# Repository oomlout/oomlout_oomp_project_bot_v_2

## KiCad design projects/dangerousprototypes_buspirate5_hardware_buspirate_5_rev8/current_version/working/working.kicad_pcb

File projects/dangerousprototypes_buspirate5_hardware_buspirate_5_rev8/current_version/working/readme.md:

# buspirate5_hardware
 
## summary 
* id: dangerousprototypes_buspirate5_hardware_buspirate_5_rev8
* user: dangerousprototypes
* name: buspirate5_hardware
* board: buspirate_5_rev8
* repo: https://github.com/DangerousPrototypes/BusPirate5-hardware
* src_file_repo_kicad_pcb: pcb/BusPirate-5-rev8.kicad_pcb
* src_file_repo_kicad_pcb_link: https://github.com/DangerousPrototypes/BusPirate5-hardware/tree/main/pcb/BusPirate-5-rev8.kicad_pcb

* src_file_repo_sch: debug-station/programming_pin_mount.v1.0.sch
* src_file_repo_sch_link: https://github.com/DangerousPrototypes/BusPirate5-hardware/tree/main/debug-station/programming_pin_mount.v1.0.sch
* full details link: https://github.com/oomlout/oomlout_oomp_project_bot_v_2/tree/main/projects/dangerousprototypes_buspirate5_hardware_buspirate_5_rev8/current_version/working  

## schematic  
  
[schematic (pdf)](working_schematic.pdf) 

[schematic 1 (pdf)](working_1_schematic.pdf) 

[schematic 2 (pdf)](working_2_schematic.pdf) 

[schematic 3 (pdf)](working_3_schematic.pdf) 

[schematic 4 (pdf)](working_4_schematic.pdf) 

[schematic 5 (pdf)](working_5_schematic.pdf) 

## pcb  

[board (pdf)](working.pdf)  

## working_bom
| Id | Designator | Footprint | Quantity | Designation | Supplier and ref |  | None | 
| --- | --- | --- | --- | --- | --- | --- | --- | 
| 1 | LED702,LED715,LED714,LED703,LED705,LED718,LED706,LED710,LED713 | SK6812-mini-e | 9 | SK6812-mini-e |  |  | [''] | 
| 2 | C402,C101,C202,C201,C401,C102,C404,C407 | C_0402_1005Metric | 8 | 4.7uF |  |  | [''] | 
| 3 | C313,C308,C315,C304,C403,C314,C309,C112,C114,C110,C111,C113,C103,C118,C705,C708,C704,C706,C710,C712,C703,C701,C117,C501,C116,C715,C714,C716,C717,C718,C318,C502,C713,C406,C115,C707,C602,C605,C702,C311,C312,C503,C306,C307,C301,C302,C305,C303,C316,C317,C310,C414,C415,C416 | C_0402_1005Metric | 54 | 0.1uF |  |  | [''] | 
| 4 | C107,C108,C109,C104,C405,C601,C413 | C_0402_1005Metric | 7 | 2.2uF |  |  | [''] | 
| 5 | C106,C105 | C_0402_1005Metric | 2 | 15pF |  |  | [''] | 
| 6 | U301,U304,U305,U307,U306,U303,U302,U308 | SOT-363_SC-70-6 | 8 | SN74LVC1T45DCK |  |  | [''] | 
| 7 | R203,R202 | R_0402_1005Metric | 2 | 22R |  |  | [''] | 
| 8 | R204,R201 | R_0402_1005Metric | 2 | 5.1K |  |  | [''] | 
| 9 | L201 | L_0805_2012Metric | 1 | 1.5A |  |  | [''] | 
| 10 | R407,R501,R402,R406,R104,R105,R410,R611,R609,R606,R610,R613,R106,R312,R414,R415 | R_0402_1005Metric | 16 | 10K |  |  | [''] | 
| 11 | R103,R608,R612,R208 | R_0402_1005Metric | 4 | 200R |  |  | [''] | 
| 12 | U103 | RP2040-QFN-56 | 1 | RP2040 |  |  | [''] | 
| 13 | U501,U502 | TSSOP-16_4.4x5mm_P0.65mm | 2 | 74HC595 |  |  | [''] | 
| 14 | RN302,RN307,RN304,RN310 | R_Array_Convex_4x0402 | 4 | 1M |  |  | [''] | 
| 15 | R209 | R_0805_2012Metric | 1 | 33R |  |  | [''] | 
| 16 | U102 | SOP-8_5.28x5.23mm_P1.27mm | 1 | W25Q128JVSIQ |  |  | [''] | 
| 17 | U310,U309 | TSSOP-14_4.4x5mm_P0.65mm | 2 | 74HC4066 |  |  | [''] | 
| 18 | R101,R602,R603,R502 | R_0402_1005Metric | 4 | 1K |  |  | [''] | 
| 19 | FID1,FID2,FID4,FID5,FID3 | Fiducial_1mm_Mask2mm | 5 | Fiducial |  |  | [''] | 
| 20 | J201 | PinSocket_1x03_P2.54mm_Vertical | 1 | Conn_01x03 |  |  | [''] | 
| 21 | R102 | R_0402_1005Metric | 1 | DNF |  |  | [''] | 
| 22 | J302 | JST_SH_SM09B-SRSS-TB_1x09-1MP_P1.00mm_Horizontal | 1 | Conn_01x09 |  |  | [''] | 
| 23 | U503 | TSSOP-20_4.4x6.5mm_P0.65mm | 1 | 74HCT245PW |  |  | [''] | 
| 24 | Y101 | Crystal_SMD_3225-4Pin_3.2x2.5mm | 1 | 12Mhz |  |  | [''] | 
| 25 | Q202 | SOT-23 | 1 | 2N7002 |  |  | [''] | 
| 26 | L100 | L_0603_1608Metric | 1 | 22uH |  |  | [''] | 
| 27 | J101 | TF-01A_C91145 | 1 | Micro_SD_Card_TF-01A_C91145 |  |  | [''] | 
| 28 | SW101 | SW_SPST_PTS810 | 1 | SW_SPST |  |  | [''] | 
| 29 | D601,D401,D603,D602 | D_SOD-323 | 4 | 1N4148WS |  |  | [''] | 
| 30 | R405,R409,R408,R605,R604 | R_0402_1005Metric | 5 | 33K |  |  | [''] | 
| 31 | R412,R401 | R_0402_1005Metric | 2 | 100K |  |  | [''] | 
| 32 | R403 | R_0402_1005Metric | 1 | 102K |  |  | [''] | 
| 33 | U601,U404,U603 | SOT-23-5 | 3 | GS6001 |  |  | [''] | 
| 34 | R601 | R_2512_6332Metric_Pad1.40x3.35mm_HandSolder | 1 | 0R2 |  |  | [''] | 
| 35 | C603 | C_0402_1005Metric | 1 | DNF |  |  | [''] | 
| 36 | U602 | SOT-23-5 | 1 | RS8901XF |  |  | [''] | 
| 37 | Q402,Q602 | SOT-23 | 2 | WST3423 |  |  | [''] | 
| 38 | U403 | SOT-23-5 | 1 | AP2127 |  |  | [''] | 
| 39 | Q601 | SOT-363_SC-70-6 | 1 | MMDT3906 |  |  | [''] | 
| 40 | Q401 | SOT-363_SC-70-6 | 1 | BCM857 |  |  | [''] | 
| 41 | RN309,RN301,RN306,RN315,RN318,RN317,RN305,RN400,RN401,RN402 | R_Array_Convex_4x0402 | 10 | 330R |  |  | [''] | 
| 42 | U402 | TSSOP-24_4.4x7.8mm_P0.65mm | 1 | 74HC4067 |  |  | [''] | 
| 43 | RN303,RN308 | R_Array_Convex_4x0402 | 2 | 100K |  |  | [''] | 
| 44 | J202 | HRO_TYPE-C-31-M-12 | 1 | TYPE-C-31-M-12 |  |  | [''] | 
| 45 | RN313,RN314,RN312,RN311 | R_Array_Convex_4x0402 | 4 | 10K |  |  | [''] | 
| 46 | LED707,LED716,LED717,LED712,LED708,LED701,LED704 | SK6812-side-a_b | 7 | SK6812-side-a_b |  |  | [''] | 
| 47 | R316,R416 | R_0402_1005Metric | 2 | 330R |  |  | [''] | 
| 48 | U401 | SOT-89-3 | 1 | ME6211A33PG-N |  |  | [''] | 
| 49 | C408 | C_0402_1005Metric | 1 | 120pF |  |  | [''] | 
| 50 | R404 | R_0402_1005Metric | 1 | 133K |  |  | [''] | 
| 51 | J301 | PinHeader_1x10_P2.54mm_Vertical | 1 | Conn_01x10 |  |  | [''] | 
| 52 | SW102 | GT-TC026X-HXXX-LX | 1 | 4P_button_sw |  |  | [''] | 
| 53 | LCD201 | TFT_20_QT200H1201 | 1 | TFT_20_QT200H1201 |  |  | [''] | 
| 54 | logo1 | logo_fcc | 1 | fcc_logo |  |  | [''] | 

## bom_schematic
| Ref | Qnty | Value | Cmp name | Footprint | Description | Vendor | DNP | 
| --- | --- | --- | --- | --- | --- | --- | --- | 
| C101, C102, C201, C202, C401, C402, C404, C407 | 8 | 4.7uF | C_Small | Capacitor_SMD:C_0402_1005Metric | Unpolarized capacitor, small symbol |  |  | 
| C103, C110, C111, C112, C113, C114, C115, C116, C117, C118, C301, C302, C303, C304, C305, C306, C307, C308, C309, C310, C311, C312, C313, C314, C315, C316, C317, C318, C403, C406, C414, C415, C416, C501, C502, C503, C602, C605, C701, C702, C703, C704, C705, C706, C707, C708, C710, C712, C713, C714, C715, C716, C717, C718 | 54 | 0.1uF | C_Small | Capacitor_SMD:C_0402_1005Metric | Unpolarized capacitor, small symbol |  |  | 
| C104, C107, C108, C109, C405, C413, C601 | 7 | 2.2uF | C_Small | Capacitor_SMD:C_0402_1005Metric | Unpolarized capacitor, small symbol |  |  | 
| C105, C106 | 2 | 15pF | C_Small | Capacitor_SMD:C_0402_1005Metric | Unpolarized capacitor, small symbol |  |  | 
| C408 | 1 | 120pF | C_Small | Capacitor_SMD:C_0402_1005Metric | Unpolarized capacitor, small symbol |  |  | 
| C603 | 1 | DNF | C_Small | Capacitor_SMD:C_0402_1005Metric | Unpolarized capacitor, small symbol |  |  | 
| D401, D601, D602, D603 | 4 | 1N4148WS | 1N4148WS | Diode_SMD:D_SOD-323 | 75V 0.15A Fast switching Diode, SOD-323 |  |  | 
| FID1, FID2, FID3, FID4, FID5 | 5 | Fiducial | Fiducial | Fiducial:Fiducial_1mm_Mask2mm | Fiducial Marker |  |  | 
| H1, H2, H3, H4 | 4 | MountingHole | MountingHole | MountingHole:MountingHole_3.2mm_M3 | Mounting Hole without connection |  |  | 
| J101 | 1 | Micro_SD_Card_TF-01A_C91145 | Micro_SD_Card_TF-01A_C91145-dp-microsd | dp-microsd:TF-01A_C91145 |  |  |  | 
| J201 | 1 | Conn_01x03 | Conn_01x03 | Connector_PinSocket_2.54mm:PinSocket_1x03_P2.54mm_Vertical | Generic connector, single row, 01x03, script generated (kicad-library-utils/schlib/autogen/connector/) |  |  | 
| J202 | 1 | TYPE-C-31-M-12 | TYPE-C-31-M-12-usb-c | HRO_TYPE-C-31-M-12 |  |  |  | 
| J301 | 1 | Conn_01x10 | Conn_01x10 | Connector_PinHeader_2.54mm:PinHeader_1x10_P2.54mm_Vertical | Generic connector, single row, 01x10, script generated (kicad-library-utils/schlib/autogen/connector/) |  |  | 
| J302 | 1 | Conn_01x09 | Conn_01x09 | Connector_JST:JST_SH_SM09B-SRSS-TB_1x09-1MP_P1.00mm_Horizontal | Generic connector, single row, 01x09, script generated (kicad-library-utils/schlib/autogen/connector/) |  |  | 
| L100 | 1 | 22uH | L_Small | Inductor_SMD:L_0603_1608Metric | Inductor, small symbol |  |  | 
| L201 | 1 | 1.5A | Ferrite_Bead_Small-kicad5-device | Inductor_SMD:L_0805_2012Metric |  |  |  | 
| LCD201 | 1 | TFT_20_QT200H1201 | TFT_20_QT200H1201-dp-lcd | dp-lcd:TFT_20_QT200H1201 |  |  |  | 
| LED1, LED2, LED3, LED4, LED5, LED6, LED7, LED8, LED9 | 9 | SK6812-mini-e | SK6812-mini-e-dp-LED | dp-LED:SK6812-mini-e |  |  |  | 
| LED701, LED704, LED707, LED708, LED712, LED716, LED717 | 7 | SK6812-side-a_b | SK6812-side-a_b-dp-LED | dp-LED:SK6812-side-a_b |  |  |  | 
| logo1 | 1 | fcc_logo | fcc_logo-DP_logo_kicad | dp-logo:logo_fcc |  |  |  | 
| Q1 | 1 | 2N7002 | BSS138 | Package_TO_SOT_SMD:SOT-23 | 50V Vds, 0.22A Id, N-Channel MOSFET, SOT-23 |  |  | 
| Q401 | 1 | BCM857 | Q_DUAL_PNP_PNP_E1B1C2E2B2C1-kicad5-device | Package_TO_SOT_SMD:SOT-363_SC-70-6 |  |  |  | 
| Q402, Q602 | 2 | WST3423 | AO3401A | Package_TO_SOT_SMD:SOT-23 | -4.0A Id, -30V Vds, P-Channel MOSFET, SOT-23 |  |  | 
| Q601 | 1 | MMDT3906 | Q_DUAL_PNP_PNP_E1B1C2E2B2C1-kicad5-device | Package_TO_SOT_SMD:SOT-363_SC-70-6 |  |  |  | 
| R1, R2, R4, R104, R105, R402, R406, R407, R410, R414, R415, R606, R609, R610, R611, R613 | 16 | 10K | R_Small | Resistor_SMD:R_0402_1005Metric | Resistor, small symbol |  |  | 
| R3, R416 | 2 | 330R | R_Small | Resistor_SMD:R_0402_1005Metric | Resistor, small symbol |  |  | 
| R5, R101, R602, R603 | 4 | 1K | R_Small | Resistor_SMD:R_0402_1005Metric | Resistor, small symbol |  |  | 
| R102 | 1 | DNF | R_Small | Resistor_SMD:R_0402_1005Metric | Resistor, small symbol |  |  | 
| R103, R208, R608, R612 | 4 | 200R | R_Small | Resistor_SMD:R_0402_1005Metric | Resistor, small symbol |  |  | 
| R201, R204 | 2 | 5.1K | R_Small | Resistor_SMD:R_0402_1005Metric | Resistor, small symbol |  |  | 
| R202, R203 | 2 | 22R | R_Small | Resistor_SMD:R_0402_1005Metric | Resistor, small symbol |  |  | 
| R209 | 1 | 33R | R_Small | Resistor_SMD:R_0805_2012Metric | Resistor, small symbol |  |  | 
| R401, R412 | 2 | 100K | R_Small | Resistor_SMD:R_0402_1005Metric | Resistor, small symbol |  |  | 
| R403 | 1 | 102K | R_Small | Resistor_SMD:R_0402_1005Metric | Resistor, small symbol |  |  | 
| R404 | 1 | 133K | R_Small | Resistor_SMD:R_0402_1005Metric | Resistor, small symbol |  |  | 
| R405, R408, R409, R604, R605 | 5 | 33K | R_Small | Resistor_SMD:R_0402_1005Metric | Resistor, small symbol |  |  | 
| R601 | 1 | 0R2 | R | Resistor_SMD:R_2512_6332Metric_Pad1.40x3.35mm_HandSolder | Resistor |  |  | 
| RN301, RN305, RN306, RN309, RN315, RN317, RN318, RN400, RN401, RN402 | 10 | 330R | R_Array-dp-rarray | Resistor_SMD:R_Array_Convex_4x0402 |  |  |  | 
| RN302, RN304, RN307, RN310 | 4 | 1M | R_Array-dp-rarray | Resistor_SMD:R_Array_Convex_4x0402 |  |  |  | 
| RN303, RN308 | 2 | 100K | R_Array-dp-rarray | Resistor_SMD:R_Array_Convex_4x0402 |  |  |  | 
| RN311, RN312, RN313, RN314 | 4 | 10K | R_Array-dp-rarray | Resistor_SMD:R_Array_Convex_4x0402 |  |  |  | 
| SW101 | 1 | SW_SPST | SW_SPST | Button_Switch_SMD:SW_SPST_PTS810 | Single Pole Single Throw (SPST) switch |  |  | 
| SW102 | 1 | 4P_button_sw | 4P_button_sw-dp-switch | dp-switch:GT-TC026X-HXXX-LX |  |  |  | 
| U102 | 1 | W25Q128JVSIQ | xm25qh128a-dp-memory | Package_SO:SOP-8_5.28x5.23mm_P1.27mm |  |  |  | 
| U103 | 1 | RP2040 | RP2040-RP_Silicon | RP_Silicon:RP2040-QFN-56 |  |  |  | 
| U301, U302, U303, U304, U305, U306, U307, U308 | 8 | SN74LVC1T45DCK | SN74LVC1T45DCK | Package_TO_SOT_SMD:SOT-363_SC-70-6 | Single-Bit Dual-Supply Bus Transceiver With Configurable Voltage Translation and 3-State Outputs, SOT-363 |  |  | 
| U309, U310 | 2 | 74HC4066 | 4066-4xxx_IEEE | Package_SO:TSSOP-14_4.4x5mm_P0.65mm |  |  |  | 
| U401 | 1 | ME6211A33PG-N | AP2204RA-3.3 | Package_TO_SOT_SMD:SOT-89-3 | 150mA low dropout linear regulator, wide input voltage range, 3.3V fixed positive output, SOT-89-3 package |  |  | 
| U402 | 1 | 74HC4067 | CD74HC4067M | Package_SO:TSSOP-24_4.4x7.8mm_P0.65mm | High-Speed CMOS Logic 16-Channel Analog Multiplexer/Demultiplexer, SOIC-24 |  |  | 
| U403 | 1 | AP2127 | MCP1824-dp-vreg | Package_TO_SOT_SMD:SOT-23-5 |  |  |  | 
| U404, U601, U603 | 3 | GS6001 | MCP6001-OT | Package_TO_SOT_SMD:SOT-23-5 | 1MHz, Low-Power Op Amp, SOT-23-5 |  |  | 
| U501, U502 | 2 | 74HC595 | 74AHCT595 | Package_SO:TSSOP-16_4.4x5mm_P0.65mm | 8-bit serial in/out Shift Register 3-State Outputs |  |  | 
| U503 | 1 | 74HCT245PW | 74HC245 | Package_SO:TSSOP-20_4.4x6.5mm_P0.65mm | Octal BUS Transceivers, 3-State outputs |  |  | 
| U602 | 1 | RS8901XF | MCP6001x-LT | Package_TO_SOT_SMD:SOT-23-5 | 1 MHz, Low-Power Op Amp, SC-70-5 |  |  | 
| Y101 | 1 | 12Mhz | Crystal_GND24_Small | Crystal:Crystal_SMD_3225-4Pin_3.2x2.5mm | Four pin crystal, GND on pins 2 and 4, small symbol |  |  |

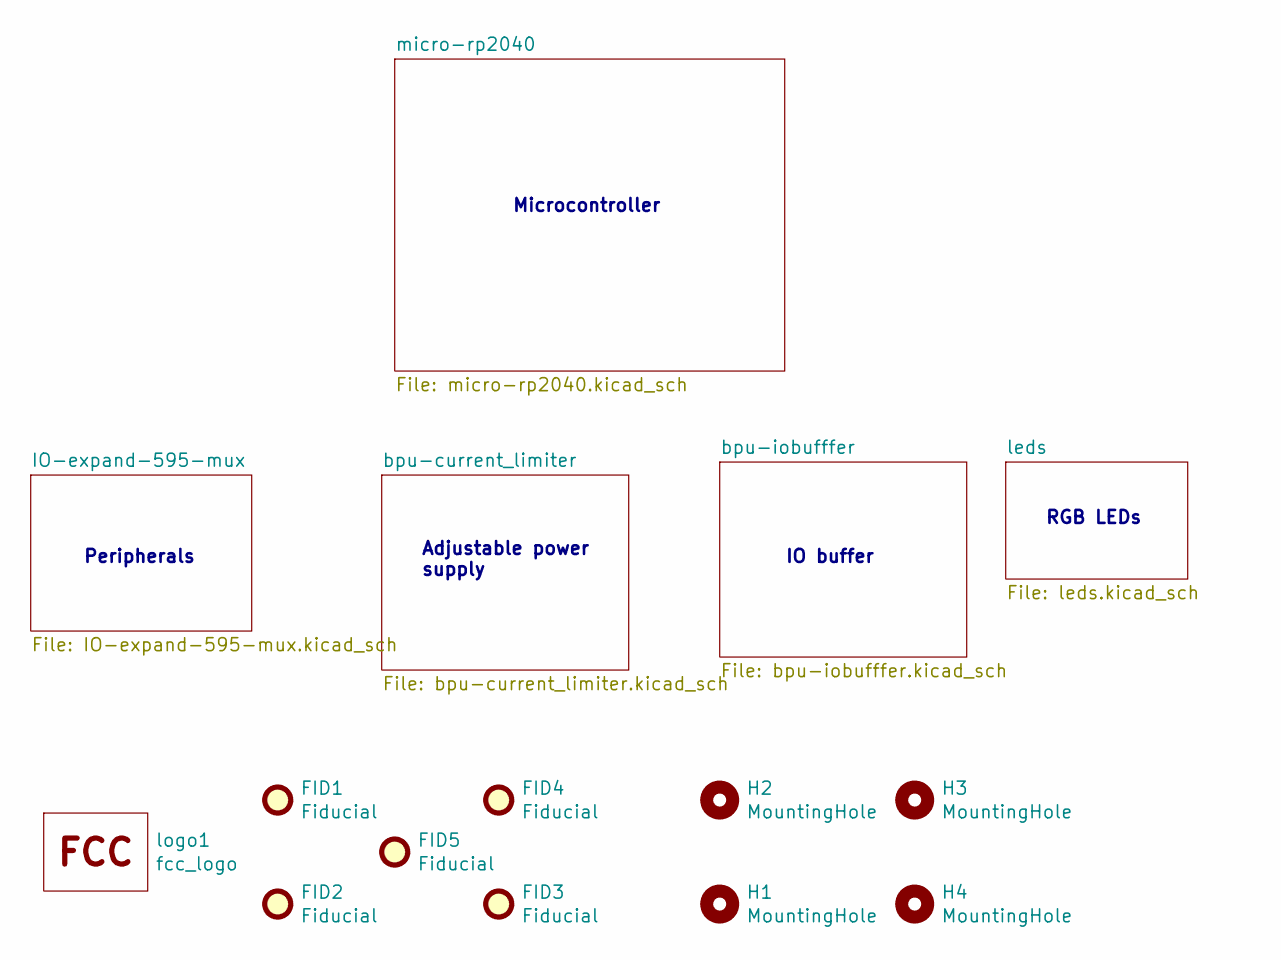
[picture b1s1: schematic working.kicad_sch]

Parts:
FID1, FID2, FID3, FID4, FID5: Fiducial; Fiducial_1mm_Mask2mm
H1, H2, H3, H4: MountingHole; MountingHole_3.2mm_M3
logo1: fcc_logo; logo_fcc

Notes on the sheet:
IO buffer
Peripherals
Adjustable power supply
Microcontroller
RGB LEDs

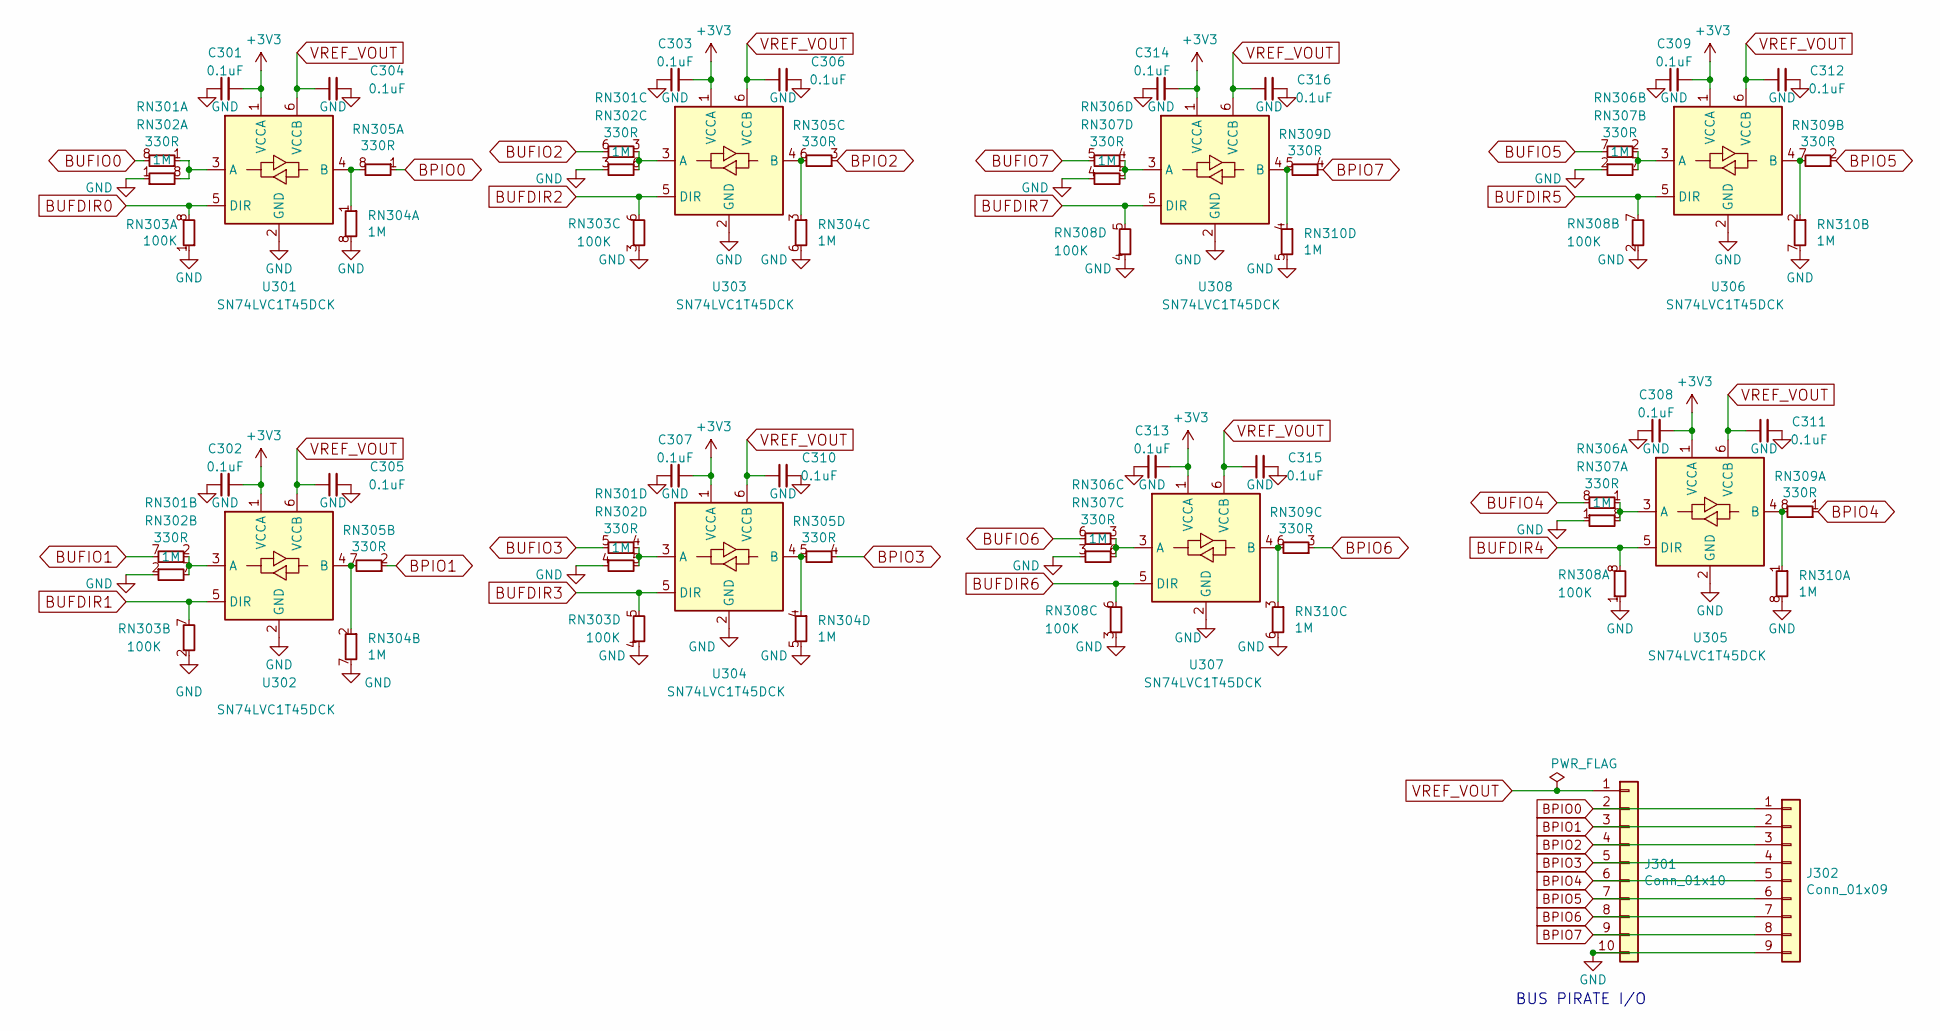
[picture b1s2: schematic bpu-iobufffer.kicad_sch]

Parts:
C301, C302, C303, C304, C305, C306, C307, C308, C309, C310, C311, C312, C313, C314, C315, C316: 0.1uF; C_0402_1005Metric
J301: Conn_01x10; PinHeader_1x10_P2.54mm_Vertical
J302: Conn_01x09; JST_SH_SM09B-SRSS-TB_1x09-1MP_P1.00mm_Horizontal
RN301, RN305, RN306, RN309: 330R; R_Array_Convex_4x0402
RN302, RN304, RN307, RN310: 1M; R_Array_Convex_4x0402
RN303, RN308: 100K; R_Array_Convex_4x0402
U301, U302, U303, U304, U305, U306, U307, U308: SN74LVC1T45DCK; SOT-363_SC-70-6

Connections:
BPIO0: J301.2, J302.1, RN305.1 (R1.1); also elsewhere on the board
BPIO1: J301.3, J302.2, RN305.2 (R1.1); also elsewhere on the board
BPIO2: J301.4, J302.3, RN305.3 (R1.1); also elsewhere on the board
BPIO3: J301.5, J302.4, RN305.4 (R1.1); also elsewhere on the board
BPIO4: J301.6, J302.5, RN309.1 (R1.1); also elsewhere on the board
BPIO5: J301.7, J302.6, RN309.2 (R1.1); also elsewhere on the board
BPIO6: J301.8, J302.7, RN309.3 (R1.1); also elsewhere on the board
BPIO7: J301.9, J302.8, RN309.4 (R1.1); also elsewhere on the board
BUFDIR0: RN303.8 (R1.8), U301.5 (DIR); also elsewhere on the board
BUFDIR1: RN303.7 (R1.8), U302.5 (DIR); also elsewhere on the board
BUFDIR2: RN303.6 (R1.8), U303.5 (DIR); also elsewhere on the board
BUFDIR3: RN303.5 (R1.8), U304.5 (DIR); also elsewhere on the board
BUFDIR4: RN308.8 (R1.8), U305.5 (DIR); also elsewhere on the board
BUFDIR5: RN308.7 (R1.8), U306.5 (DIR); also elsewhere on the board
BUFDIR6: RN308.6 (R1.8), U307.5 (DIR); also elsewhere on the board
BUFDIR7: RN308.5 (R1.8), U308.5 (DIR); also elsewhere on the board
BUFIO0: RN301.8 (R1.8); also elsewhere on the board
BUFIO1: RN301.7 (R1.8); also elsewhere on the board
BUFIO2: RN301.6 (R1.8); also elsewhere on the board
BUFIO3: RN301.5 (R1.8); also elsewhere on the board
BUFIO4: RN306.8 (R1.8); also elsewhere on the board
BUFIO5: RN306.7 (R1.8); also elsewhere on the board
BUFIO6: RN306.6 (R1.8); also elsewhere on the board
BUFIO7: RN306.5 (R1.8); also elsewhere on the board
GND: C301.1, C302.1, C303.1, C304.2, C305.2, C306.2, C307.1, C308.1, C309.1, C310.2, C311.2, C312.2, C313.1, C314.1, C315.2, C316.2, J301.10, J302.9, RN302.1 (R1.1), RN302.2 (R1.1), RN302.3 (R1.1), RN302.4 (R1.1), RN303.1 (R1.1), RN303.2 (R1.1), RN303.3 (R1.1), RN303.4 (R1.1), RN304.5 (R1.8), RN304.6 (R1.8), RN304.7 (R1.8), RN304.8 (R1.8), RN307.1 (R1.1), RN307.2 (R1.1), RN307.3 (R1.1), RN307.4 (R1.1), RN308.1 (R1.1), RN308.2 (R1.1), RN308.3 (R1.1), RN308.4 (R1.1), RN310.5 (R1.8), RN310.6 (R1.8), RN310.7 (R1.8), RN310.8 (R1.8), U301.2 (GND), U302.2 (GND), U303.2 (GND), U304.2 (GND), U305.2 (GND), U306.2 (GND), U307.2 (GND), U308.2 (GND); also elsewhere on the board
unnamed: RN301.1 (R1.1), RN302.8 (R1.8), U301.3 (A)
unnamed: RN301.2 (R1.1), RN302.7 (R1.8), U302.3 (A)
unnamed: RN301.3 (R1.1), RN302.6 (R1.8), U303.3 (A)
unnamed: RN301.4 (R1.1), RN302.5 (R1.8), U304.3 (A)
unnamed: RN304.1 (R1.1), RN305.8 (R1.8), U301.4 (B)
unnamed: RN304.2 (R1.1), RN305.7 (R1.8), U302.4 (B)
unnamed: RN304.3 (R1.1), RN305.6 (R1.8), U303.4 (B)
unnamed: RN304.4 (R1.1), RN305.5 (R1.8), U304.4 (B)
unnamed: RN306.1 (R1.1), RN307.8 (R1.8), U305.3 (A)
unnamed: RN306.2 (R1.1), RN307.7 (R1.8), U306.3 (A)
unnamed: RN306.3 (R1.1), RN307.6 (R1.8), U307.3 (A)
unnamed: RN306.4 (R1.1), RN307.5 (R1.8), U308.3 (A)
unnamed: RN309.5 (R1.8), RN310.4 (R1.1), U308.4 (B)
unnamed: RN309.6 (R1.8), RN310.3 (R1.1), U307.4 (B)
unnamed: RN309.7 (R1.8), RN310.2 (R1.1), U306.4 (B)
unnamed: RN309.8 (R1.8), RN310.1 (R1.1), U305.4 (B)
VREF_VOUT: C304.1, C305.1, C306.1, C310.1, C311.1, C312.1, C315.1, C316.1, J301.1, U301.6 (VCCB), U302.6 (VCCB), U303.6 (VCCB), U304.6 (VCCB), U305.6 (VCCB), U306.6 (VCCB), U307.6 (VCCB), U308.6 (VCCB); also elsewhere on the board

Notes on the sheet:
BUS PIRATE I/O

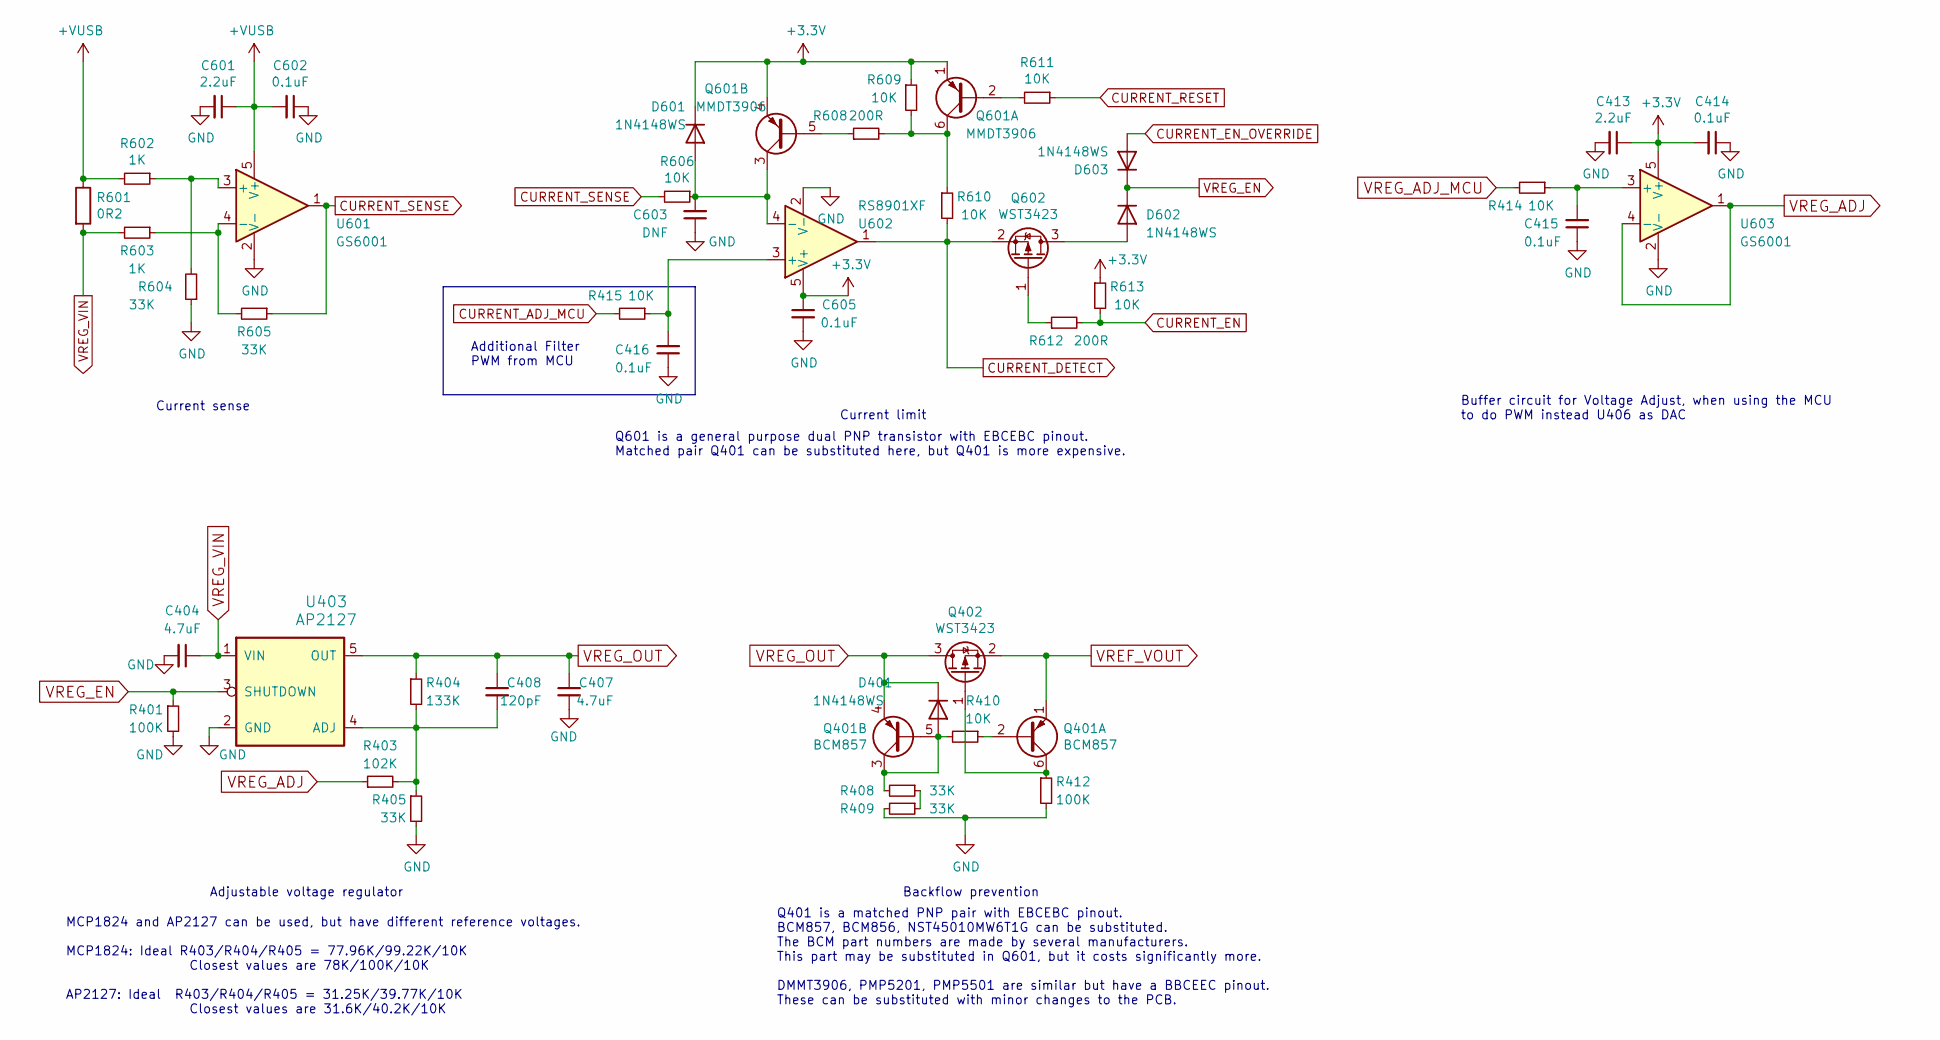
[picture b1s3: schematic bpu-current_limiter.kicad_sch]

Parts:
C404, C407: 4.7uF; C_0402_1005Metric
C408: 120pF; C_0402_1005Metric
C413, C601: 2.2uF; C_0402_1005Metric
C414, C415, C416, C602, C605: 0.1uF; C_0402_1005Metric
C603: DNF; C_0402_1005Metric
D401, D601, D602, D603: 1N4148WS; D_SOD-323
Q401: BCM857; SOT-363_SC-70-6
Q402, Q602: WST3423; SOT-23
Q601: MMDT3906; SOT-363_SC-70-6
R401, R412: 100K; R_0402_1005Metric
R403: 102K; R_0402_1005Metric
R404: 133K; R_0402_1005Metric
R405, R408, R409, R604, R605: 33K; R_0402_1005Metric
R410, R414, R415, R606, R609, R610, R611, R613: 10K; R_0402_1005Metric
R601: 0R2; R_2512_6332Metric_Pad1.40x3.35mm_HandSolder
R602, R603: 1K; R_0402_1005Metric
R608, R612: 200R; R_0402_1005Metric
U403: AP2127; SOT-23-5
U601, U603: GS6001; SOT-23-5
U602: RS8901XF; SOT-23-5

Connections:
+VUSB: C601.1, C602.2, R601.1, R602.2, U601.5 (V+); also elsewhere on the board
CURRENT_ADJ_MCU: R415.2; also elsewhere on the board
CURRENT_DETECT: Q602.2 (S), R610.2, U602.1; also elsewhere on the board
CURRENT_EN: R612.2, R613.2; also elsewhere on the board
CURRENT_EN_OVERRIDE: D603.2 (A); also elsewhere on the board
CURRENT_RESET: R611.1; also elsewhere on the board
CURRENT_SENSE: R605.1, R606.2, U601.1; also elsewhere on the board
GND: C404.2, C407.2, C413.2, C414.1, C415.1, C416.1, C601.2, C602.1, C603.1, C605.2, R401.2, R405.2, R409.2, R412.2, R604.1, U403.2 (GND), U601.2 (V-), U602.2 (V-), U603.2 (V-); also elsewhere on the board
unnamed: C408.2, R403.2, R404.2, R405.1, U403.4 (ADJ)
unnamed: C415.2, R414.1, U603.3 (+)
unnamed: C416.2, R415.1, U602.3 (+)
unnamed: C603.2, D601.2 (A), Q601.3 (C2), R606.1, U602.4 (-)
unnamed: D401.2 (A), Q401.3 (C2), Q401.5 (B2), R408.2, R410.2
unnamed: D602.2 (A), Q602.3 (D)
unnamed: Q401.2 (B1), R410.1
unnamed: Q401.6 (C1), Q402.1 (G), R412.1
unnamed: Q601.2 (B1), R611.2
unnamed: Q601.5 (B2), R608.1
unnamed: Q601.6 (C1), R608.2, R609.2, R610.1
unnamed: Q602.1 (G), R612.1
unnamed: R408.1, R409.1
unnamed: R602.1, R604.2, U601.3 (+)
unnamed: R603.1, R605.2, U601.4 (-)
VREF_VOUT: Q401.1 (E1), Q402.2 (S); also elsewhere on the board
VREG_ADJ: R403.1, U603.1, U603.4 (-)
VREG_ADJ_MCU: R414.2; also elsewhere on the board
VREG_EN: D602.1 (K), D603.1 (K), R401.1, U403.3 (SHUTDOWN)
VREG_OUT: C407.1, C408.1, D401.1 (K), Q401.4 (E2), Q402.3 (D), R404.1, U403.5 (OUT); also elsewhere on the board
VREG_VIN: C404.1, R601.2, R603.2, U403.1 (VIN)

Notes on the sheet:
Backflow prevention
Q401 is a matched PNP pair with EBCEBC pinout. BCM857, BCM856, NST45010MW6T1G can be substituted. The BCM part numbers are made by several manufacturers. This part may be substituted in Q601, but it costs significantly more. DMMT3906, PMP5201, PMP5501 are similar but have a BBCEEC pinout. These can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
Adjustable voltage regulator
Additional Filter PWM from MCU
Current sense
MCP1824 and AP2127 can be used, but have different reference voltages. MCP1824: Ideal R403/R404/R405 = 77.96K/99.22K/10K Closest values are 78K/100K/10K AP2127: Ideal R403/R404/R405 = 31.25K/39.77K/10K Closest values are 31.6K/40.2K/10K
Buffer circuit for Voltage Adjust, when using the MCU to do PWM instead U406 as DAC
Q601 is a general purpose dual PNP transistor with EBCEBC pinout. Matched pair Q401 can be substituted here, but Q401 is more expensive.
Current limit

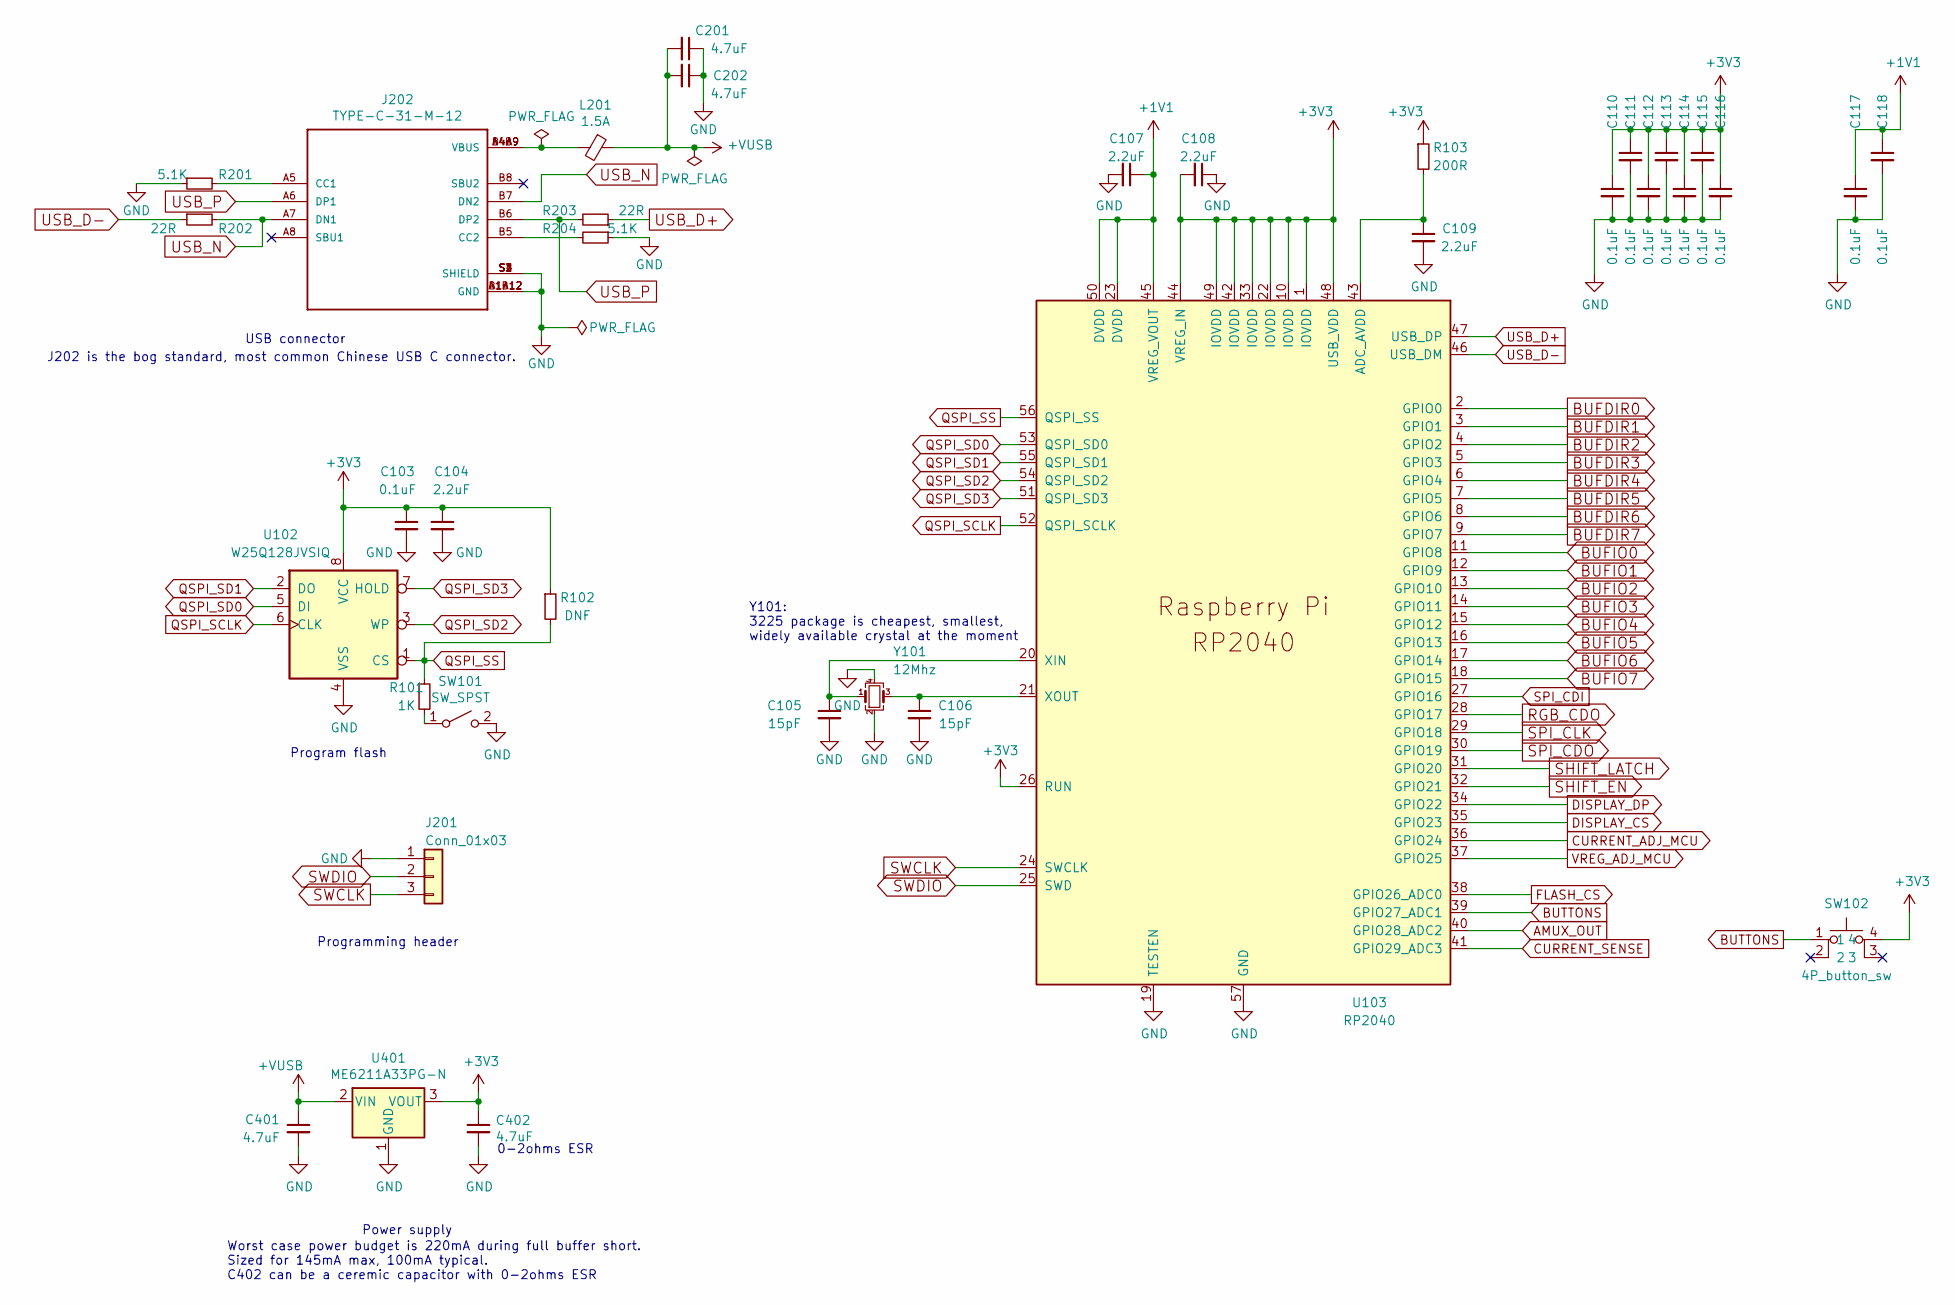
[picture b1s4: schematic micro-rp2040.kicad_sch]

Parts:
C103, C110, C111, C112, C113, C114, C115, C116, C117, C118: 0.1uF; C_0402_1005Metric
C104, C107, C108, C109: 2.2uF; C_0402_1005Metric
C105, C106: 15pF; C_0402_1005Metric
C201, C202, C401, C402: 4.7uF; C_0402_1005Metric
J201: Conn_01x03; PinSocket_1x03_P2.54mm_Vertical
J202: TYPE-C-31-M-12; HRO_TYPE-C-31-M-12
L201: 1.5A; L_0805_2012Metric
R101: 1K; R_0402_1005Metric
R102: DNF; R_0402_1005Metric
R103: 200R; R_0402_1005Metric
R201, R204: 5.1K; R_0402_1005Metric
R202, R203: 22R; R_0402_1005Metric
SW101: SW_SPST; SW_SPST_PTS810
SW102: 4P_button_sw; GT-TC026X-HXXX-LX
U102: W25Q128JVSIQ; SOP-8_5.28x5.23mm_P1.27mm
U103: RP2040; RP2040-QFN-56
U401: ME6211A33PG-N; SOT-89-3
Y101: 12Mhz; Crystal_SMD_3225-4Pin_3.2x2.5mm

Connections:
+1V1: C107.1, C117.1, C118.1, U103.23 (DVDD), U103.45 (VREG_VOUT), U103.50 (DVDD)
+VUSB: C201.2, C202.2, C401.1, L201.1, U401.2 (VIN); also elsewhere on the board
AMUX_OUT: U103.40 (GPIO28_ADC2); also elsewhere on the board
BUFDIR0: U103.2 (GPIO0); also elsewhere on the board
BUFDIR1: U103.3 (GPIO1); also elsewhere on the board
BUFDIR2: U103.4 (GPIO2); also elsewhere on the board
BUFDIR3: U103.5 (GPIO3); also elsewhere on the board
BUFDIR4: U103.6 (GPIO4); also elsewhere on the board
BUFDIR5: U103.7 (GPIO5); also elsewhere on the board
BUFDIR6: U103.8 (GPIO6); also elsewhere on the board
BUFDIR7: U103.9 (GPIO7); also elsewhere on the board
BUFIO0: U103.11 (GPIO8); also elsewhere on the board
BUFIO1: U103.12 (GPIO9); also elsewhere on the board
BUFIO2: U103.13 (GPIO10); also elsewhere on the board
BUFIO3: U103.14 (GPIO11); also elsewhere on the board
BUFIO4: U103.15 (GPIO12); also elsewhere on the board
BUFIO5: U103.16 (GPIO13); also elsewhere on the board
BUFIO6: U103.17 (GPIO14); also elsewhere on the board
BUFIO7: U103.18 (GPIO15); also elsewhere on the board
BUTTONS: SW102.1, U103.39 (GPIO27_ADC1)
CURRENT_ADJ_MCU: U103.36 (GPIO24); also elsewhere on the board
CURRENT_SENSE: U103.41 (GPIO29_ADC3); also elsewhere on the board
DISPLAY_CS: U103.35 (GPIO23); also elsewhere on the board
DISPLAY_DP: U103.34 (GPIO22); also elsewhere on the board
FLASH_CS: U103.38 (GPIO26_ADC0); also elsewhere on the board
GND: C103.2, C104.2, C105.2, C106.2, C107.2, C108.1, C109.2, C110.2, C111.2, C112.2, C113.2, C114.2, C115.2, C116.2, C117.2, C118.2, C201.1, C202.1, C401.2, C402.2, J201.1, J202.A1B12 (GND), J202.B1A12 (GND), J202.S1 (SHIELD), J202.S2 (SHIELD), J202.S3 (SHIELD), J202.S4 (SHIELD), R201.1, R204.1, SW101.2 (B), U102.4 (VSS), U103.19 (TESTEN), U103.57 (GND), U401.1 (GND), Y101.2, Y101.4; also elsewhere on the board
unnamed: C105.1, U103.20 (XIN), Y101.1
unnamed: C106.1, U103.21 (XOUT), Y101.3
unnamed: C109.1, R103.2, U103.43 (ADC_AVDD)
unnamed: J202.A4B9 (VBUS), J202.B4A9 (VBUS), L201.2
unnamed: J202.A5 (CC1), R201.2
unnamed: J202.B5 (CC2), R204.2
unnamed: R101.2, SW101.1 (A)
QSPI_SCLK: U102.6 (CLK), U103.52 (QSPI_SCLK)
QSPI_SD0: U102.5 (DI), U103.53 (QSPI_SD0)
QSPI_SD1: U102.2 (DO), U103.55 (QSPI_SD1)
QSPI_SD2: U102.3 (WP), U103.54 (QSPI_SD2)
QSPI_SD3: U102.7 (HOLD), U103.51 (QSPI_SD3)
QSPI_SS: R101.1, R102.2, U102.1 (CS), U103.56 (QSPI_SS)
RGB_CDO: U103.28 (GPIO17); also elsewhere on the board
SHIFT_EN: U103.32 (GPIO21); also elsewhere on the board
SHIFT_LATCH: U103.31 (GPIO20); also elsewhere on the board
SPI_CDI: U103.27 (GPIO16); also elsewhere on the board
SPI_CDO: U103.30 (GPIO19); also elsewhere on the board
SPI_CLK: U103.29 (GPIO18); also elsewhere on the board
SWCLK: J201.3, U103.24 (SWCLK)
SWDIO: J201.2, U103.25 (SWD)
USB_D+: R203.1, U103.47 (USB_DP)
USB_D-: R202.1, U103.46 (USB_DM)
USB_N: J202.A7 (DN1), J202.B7 (DN2), R202.2
USB_P: J202.A6 (DP1), J202.B6 (DP2), R203.2
VREG_ADJ_MCU: U103.37 (GPIO25); also elsewhere on the board

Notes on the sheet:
Y101: 3225 package is cheapest, smallest, widely available crystal at the moment
Power supply
0-2ohms ESR
J202 is the bog standard, most common Chinese USB C connector.
USB connector
Worst case power budget is 220mA during full buffer short. Sized for 145mA max, 100mA typical. C402 can be a ceremic capacitor with 0-2ohms ESR
Program flash
Programming header
